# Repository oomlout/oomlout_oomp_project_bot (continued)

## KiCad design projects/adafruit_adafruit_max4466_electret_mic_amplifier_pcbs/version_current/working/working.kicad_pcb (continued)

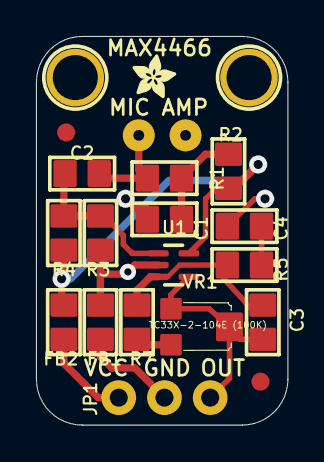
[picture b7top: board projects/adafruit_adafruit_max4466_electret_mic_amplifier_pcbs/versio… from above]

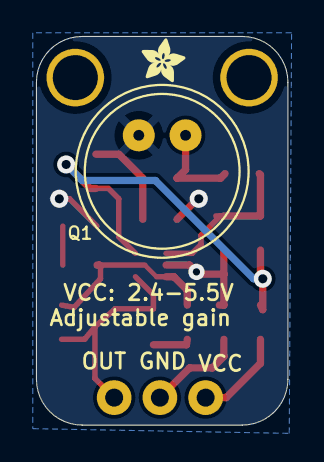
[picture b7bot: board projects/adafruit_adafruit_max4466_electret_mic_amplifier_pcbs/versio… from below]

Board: 2 copper layers, 14.0 x 21.6 mm, 22 parts (2 on the bottom side), 11 nets.

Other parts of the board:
U$16, U$17: ADAFRUIT_2.5MM

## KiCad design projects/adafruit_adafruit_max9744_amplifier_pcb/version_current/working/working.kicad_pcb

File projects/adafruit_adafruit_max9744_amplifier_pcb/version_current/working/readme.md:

# Adafruit-MAX9744-Amplifier-PCB by adafruit  
This is a harvested standardized copy of a project from github.  
The original project can be found at:  
https://github.com/adafruit/Adafruit-MAX9744-Amplifier-PCB  
Please consult that link for additional, details, files, and license information.  
Note: It was auto harvested and if the original repo had more than one board file or anything out of the ordinary the files here are likely not representative.

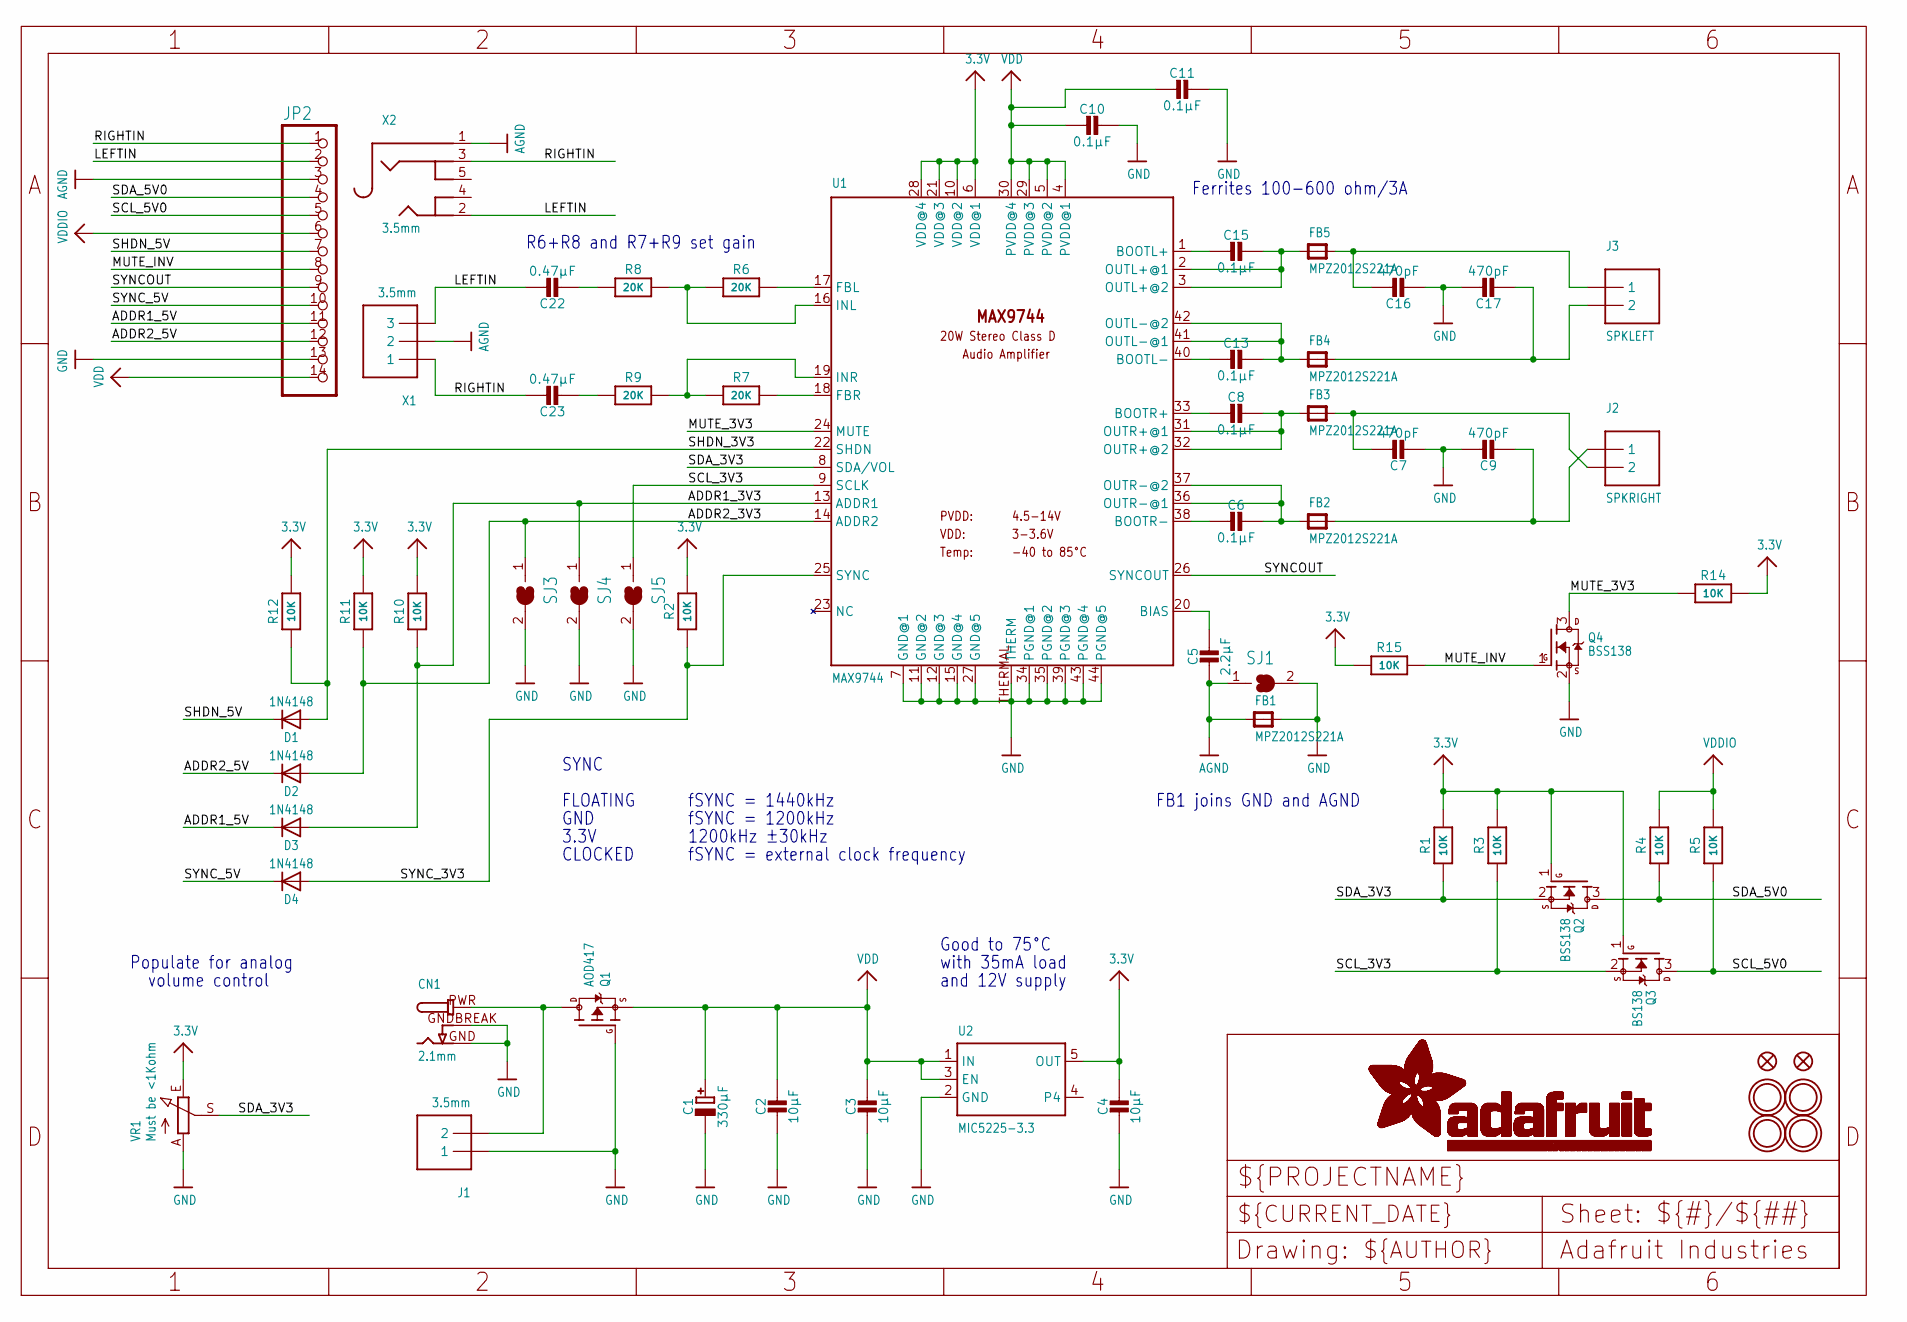
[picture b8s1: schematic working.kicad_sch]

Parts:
C1: 330µF; CELEC_3.5MM_8MM
C2, C3, C4: 10µF; 0805-NO
C5: 2.2µF; 0805-NO
C6, C8, C10, C11, C13, C15: 0.1µF; 0805-NO
C7, C9, C16, C17: 470pF; 0805-NO
C22, C23: 0.47µF; 0805-NO
CN1: 2.1mm; DCJACK_2MM_SMT
D1, D2, D3, D4: 1N4148; SOD-323
FB1, FB2, FB3, FB4, FB5: MPZ2012S221A; _0805
FID1, FID2: FIDUCIAL""; FIDUCIAL_1MM
J1: 3.5mm; TERMBLOCK_1X2-3.5MM
J2: SPKRIGHT; TERMBLOCK_1X2-3.5MM
J3: SPKLEFT; TERMBLOCK_1X2-3.5MM
JP2: HEADER-1X14; 1X14_ROUND70
Q1: AOD417; TO252
Q2, Q4: BSS138; SOT23-WIDE
Q3: BS138; SOT23-WIDE
R1, R3, R4, R5, R12: 10K; 0805-NO
R2, R10, R11, R14, R15: 10K; _0805MP
R6, R7, R8, R9: 20K; 0805-NO
SJ1, SJ3, SJ4, SJ5: SOLDERJUMPER; SOLDERJUMPER_ARROW_NOPASTE
U1: MAX9744; TQFN44_7MM
U2: MIC5225-3.3; SOT23-5
U$29, U$38, U$39, U$40: MOUNTINGHOLE2.5_THICK; MOUNTINGHOLE_2.5_PLATED_THICK
VR1: Must be <1Kohm; TRIMPOT_100MILPTH
X1: 3.5mm; TERMBLOCK_1X3-3.5MM
X2: 3.5mm; 4UCONN_19269

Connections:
3.3V: C4.1, Q2.1 (G), Q3.1 (G), R1.2, R2.2, R3.2, R10.2, R11.2, R12.2, R14.2, R15.1, U1.6 (VDD@1), U1.10 (VDD@2), U1.21 (VDD@3), U1.28 (VDD@4), U2.5 (OUT), VR1.E
ADDR1_3V3: D3.A, R10.1, SJ4.1, U1.13 (ADDR1)
ADDR1_5V: D3.C, JP2.11
ADDR2_3V3: D2.A, R11.1, SJ3.1, U1.14 (ADDR2)
ADDR2_5V: D2.C, JP2.12
AGND: C5.2, FB1.1, JP2.3, SJ1.1, X1.2, X2.1
GND: C1.-, C2.2, C3.2, C4.2, C7.2, C9.1, C10.1, C11.1, C16.2, C17.1, CN1.GND, CN1.GNDBREAK, FB1.2, J1.1, JP2.13, Q1.1 (G), Q4.2 (S), SJ1.2, SJ3.2, SJ4.2, SJ5.2, U1.7 (GND@1), U1.11 (GND@2), U1.12 (GND@3), U1.15 (GND@4), U1.27 (GND@5), U1.34 (PGND@1), U1.35 (PGND@2), U1.39 (PGND@3), U1.43 (PGND@4), U1.44 (PGND@5), U1.THERMAL (THERM), U2.2 (GND), VR1.A
LEFTIN: C22.1, JP2.2, X1.3, X2.2
MUTE_3V3: Q4.3 (D), R14.1, U1.24 (MUTE)
MUTE_INV: JP2.8, Q4.1 (G), R15.2
unnamed: CN1.PWR, J1.2, Q1.3 (D)
unnamed: C5.1, U1.20 (BIAS)
unnamed: C6.2, U1.38 (BOOTR-)
unnamed: C6.1, FB2.1, U1.36 (OUTR-@1), U1.37 (OUTR-@2)
unnamed: C8.2, U1.33 (BOOTR+)
unnamed: C8.1, FB3.1, U1.31 (OUTR+@1), U1.32 (OUTR+@2)
unnamed: C7.1, FB3.2, J2.2
unnamed: C9.2, FB2.2, J2.1
unnamed: C13.1, FB4.1, U1.41 (OUTL-@1), U1.42 (OUTL-@2)
unnamed: C15.1, FB5.1, U1.2 (OUTL+@1), U1.3 (OUTL+@2)
unnamed: C16.1, FB5.2, J3.1
unnamed: C17.2, FB4.2, J3.2
unnamed: C15.2, U1.1 (BOOTL+)
unnamed: C13.2, U1.40 (BOOTL-)
unnamed: R6.2, U1.17 (FBL)
unnamed: R7.2, U1.18 (FBR)
unnamed: R6.1, R8.2, U1.16 (INL)
unnamed: R7.1, R9.2, U1.19 (INR)
unnamed: C22.2, R8.1
unnamed: C23.2, R9.1
RIGHTIN: C23.1, JP2.1, X1.1, X2.3
SCL_3V3: Q3.2 (S), R3.1, SJ5.1, U1.9 (SCLK)
SCL_5V0: JP2.5, Q3.3 (D), R5.1
SDA_3V3: Q2.2 (S), R1.1, U1.8 (SDA/VOL), VR1.S
SDA_5V0: JP2.4, Q2.3 (D), R4.1
SHDN_3V3: D1.A, R12.1, U1.22 (SHDN)
SHDN_5V: D1.C, JP2.7
SYNCOUT: JP2.9, U1.26 (SYNCOUT)
SYNC_3V3: D4.A, R2.1, U1.25 (SYNC)
SYNC_5V: D4.C, JP2.10
VDD: C1.+, C2.1, C3.1, C10.2, C11.2, JP2.14, Q1.2 (S), U1.4 (PVDD@1), U1.5 (PVDD@2), U1.29 (PVDD@3), U1.30 (PVDD@4), U2.1 (IN), U2.3 (EN)
VDDIO: JP2.6, R4.2, R5.2

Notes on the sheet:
FB1 joins GND and AGND
CLOCKED
Populate for analog
Ferrites 100-600 ohm/3A
fSYNC = 1200kHz
with 35mA load
R6+R8 and R7+R9 set gain
SYNC
fSYNC = 1440kHz
Good to 75°C
fSYNC = external clock frequency
FLOATING
and 12V supply
3.3V
volume control
GND
1200kHz ±30kHz

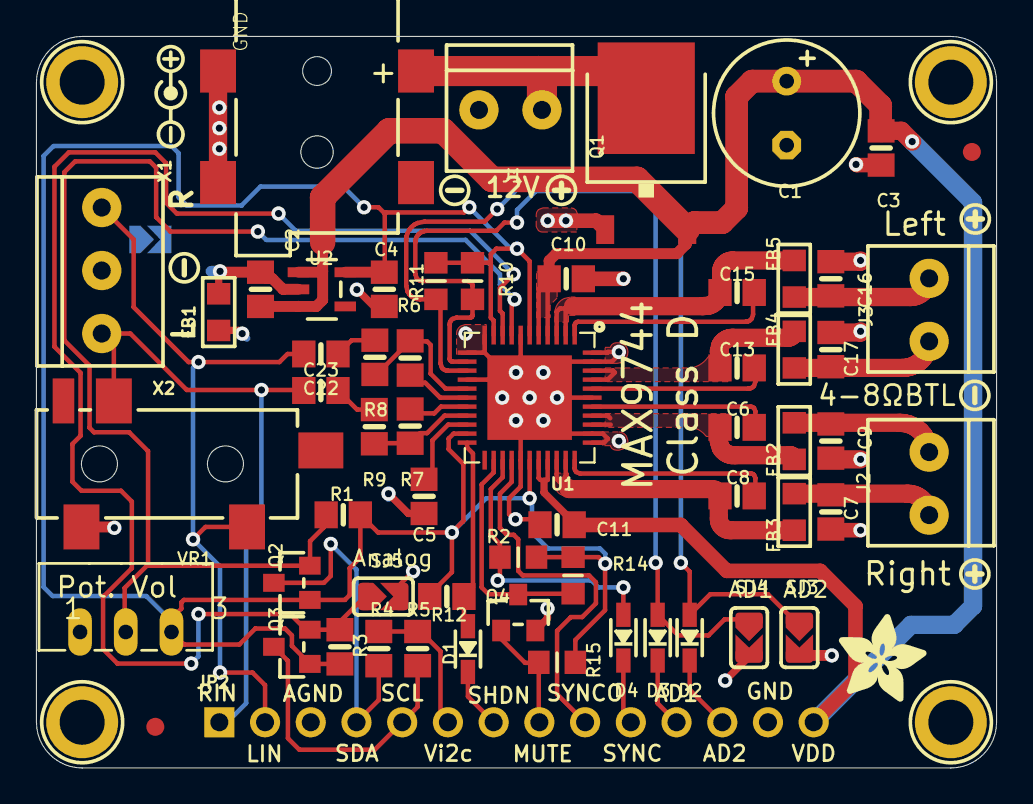
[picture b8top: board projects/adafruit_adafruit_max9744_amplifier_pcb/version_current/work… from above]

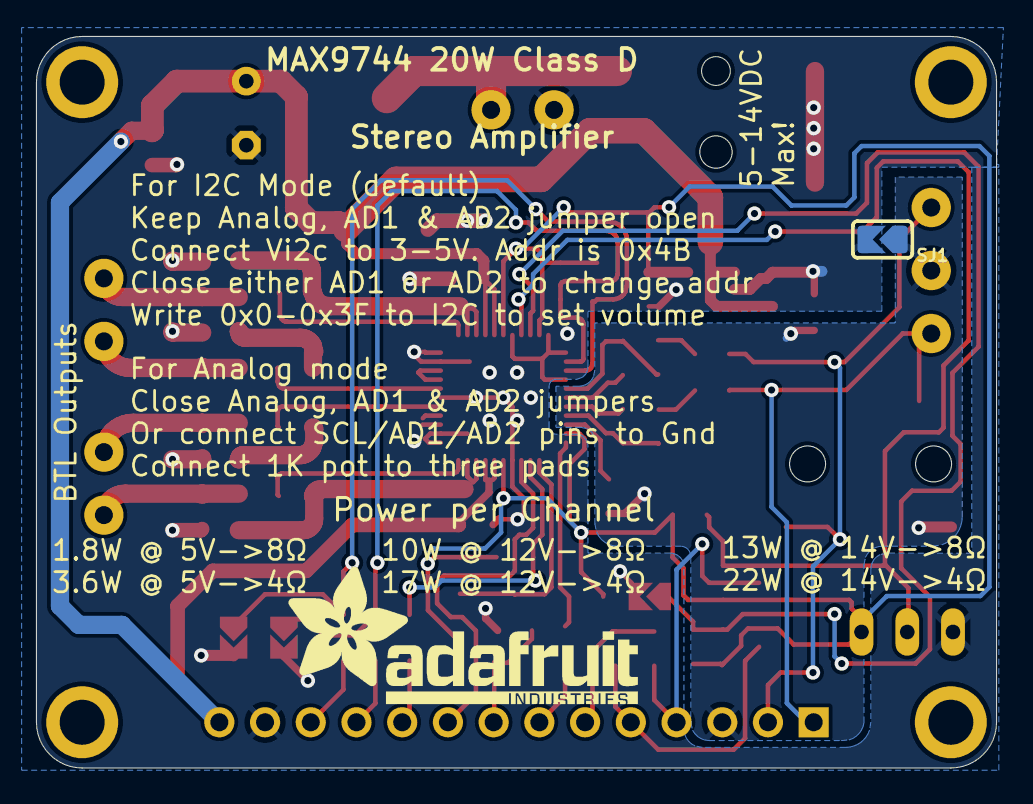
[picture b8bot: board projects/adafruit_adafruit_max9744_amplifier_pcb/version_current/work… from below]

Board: 2 copper layers, 53.3 x 40.6 mm, 73 parts (2 on the bottom side), 42 nets.

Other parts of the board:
U$28: ADAFRUIT_TEXT_20MM
U$32: ADAFRUIT_5MM
U$41: ICON_POSITIVE_CENTER-M
U$42, U$50, U$52: ICON_PLUS
U$43, U$47, U$51: ICON_MINUS
